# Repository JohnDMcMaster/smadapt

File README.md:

# smadapt
Socket module adapters

Released under CERN-OHL-P version 2

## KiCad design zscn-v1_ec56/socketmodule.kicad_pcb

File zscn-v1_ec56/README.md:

Allows using EC56 adapters in zscn hardware

Background:
-EC56: flash socket module ecosystem (https://www.embeddedcomputers.net/products/ParallelAdapters/)
-zscn: proprietary chip tester w/ SDIP64 socket

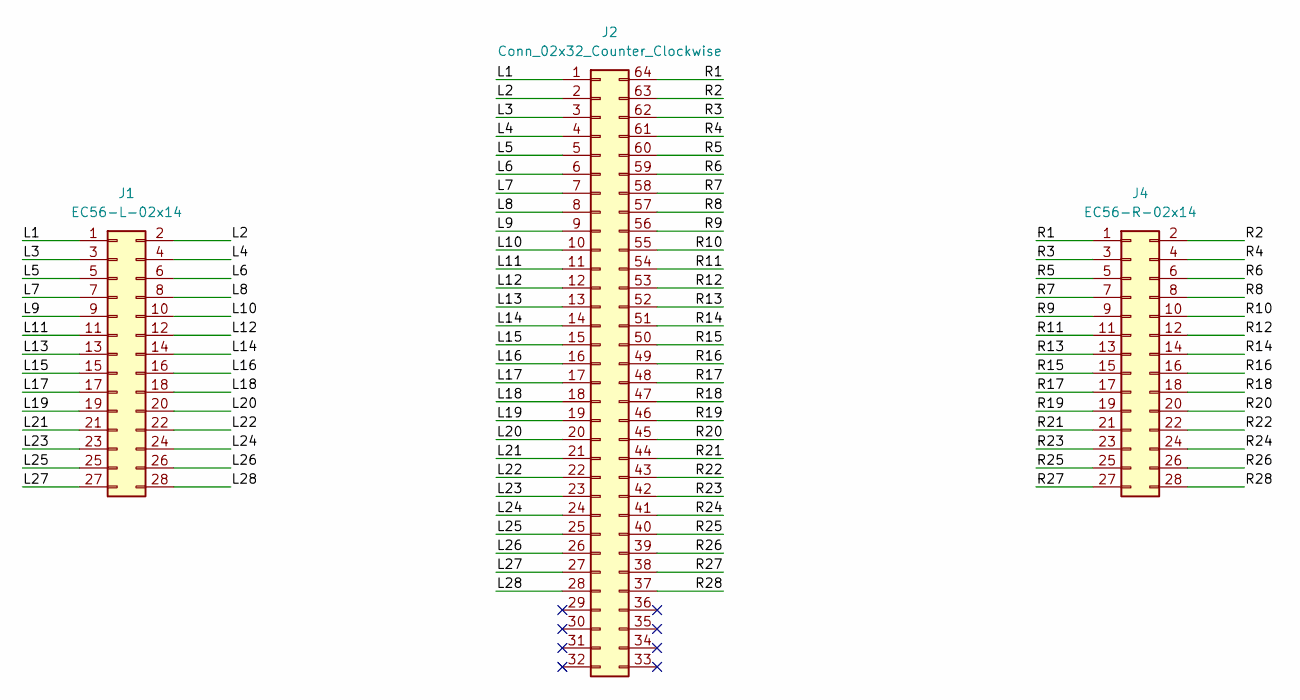
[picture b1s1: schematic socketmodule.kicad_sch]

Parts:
J1: EC56-L-02x14; PinHeader_2x14_P2.00mm_Vertical
J2: Conn_02x32_Counter_Clockwise; DIP-64_750_ELL
J4: EC56-R-02x14; PinHeader_2x14_P2.00mm_Vertical

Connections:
/L1: J1.1, J2.1
/L2: J1.2, J2.2
/L3: J1.3, J2.3
/L4: J1.4, J2.4
/L5: J1.5, J2.5
/L6: J1.6, J2.6
/L7: J1.7, J2.7
/L8: J1.8, J2.8
/L9: J1.9, J2.9
/L10: J1.10, J2.10
/L11: J1.11, J2.11
/L12: J1.12, J2.12
/L13: J1.13, J2.13
/L14: J1.14, J2.14
/L15: J1.15, J2.15
/L16: J1.16, J2.16
/L17: J1.17, J2.17
/L18: J1.18, J2.18
/L19: J1.19, J2.19
/L20: J1.20, J2.20
/L21: J1.21, J2.21
/L22: J1.22, J2.22
/L23: J1.23, J2.23
/L24: J1.24, J2.24
/L25: J1.25, J2.25
/L26: J1.26, J2.26
/L27: J1.27, J2.27
/L28: J1.28, J2.28
/R1: J2.64, J4.1
/R2: J2.63, J4.2
/R3: J2.62, J4.3
/R4: J2.61, J4.4
/R5: J2.60, J4.5
/R6: J2.59, J4.6
/R7: J2.58, J4.7
/R8: J2.57, J4.8
/R9: J2.56, J4.9
/R10: J2.55, J4.10
/R11: J2.54, J4.11
/R12: J2.53, J4.12
/R13: J2.52, J4.13
/R14: J2.51, J4.14
/R15: J2.50, J4.15
/R16: J2.49, J4.16
/R17: J2.48, J4.17
/R18: J2.47, J4.18
/R19: J2.46, J4.19
/R20: J2.45, J4.20
/R21: J2.44, J4.21
/R22: J2.43, J4.22
/R23: J2.42, J4.23
/R24: J2.41, J4.24
/R25: J2.40, J4.25
/R26: J2.39, J4.26
/R27: J2.38, J4.27
/R28: J2.37, J4.28

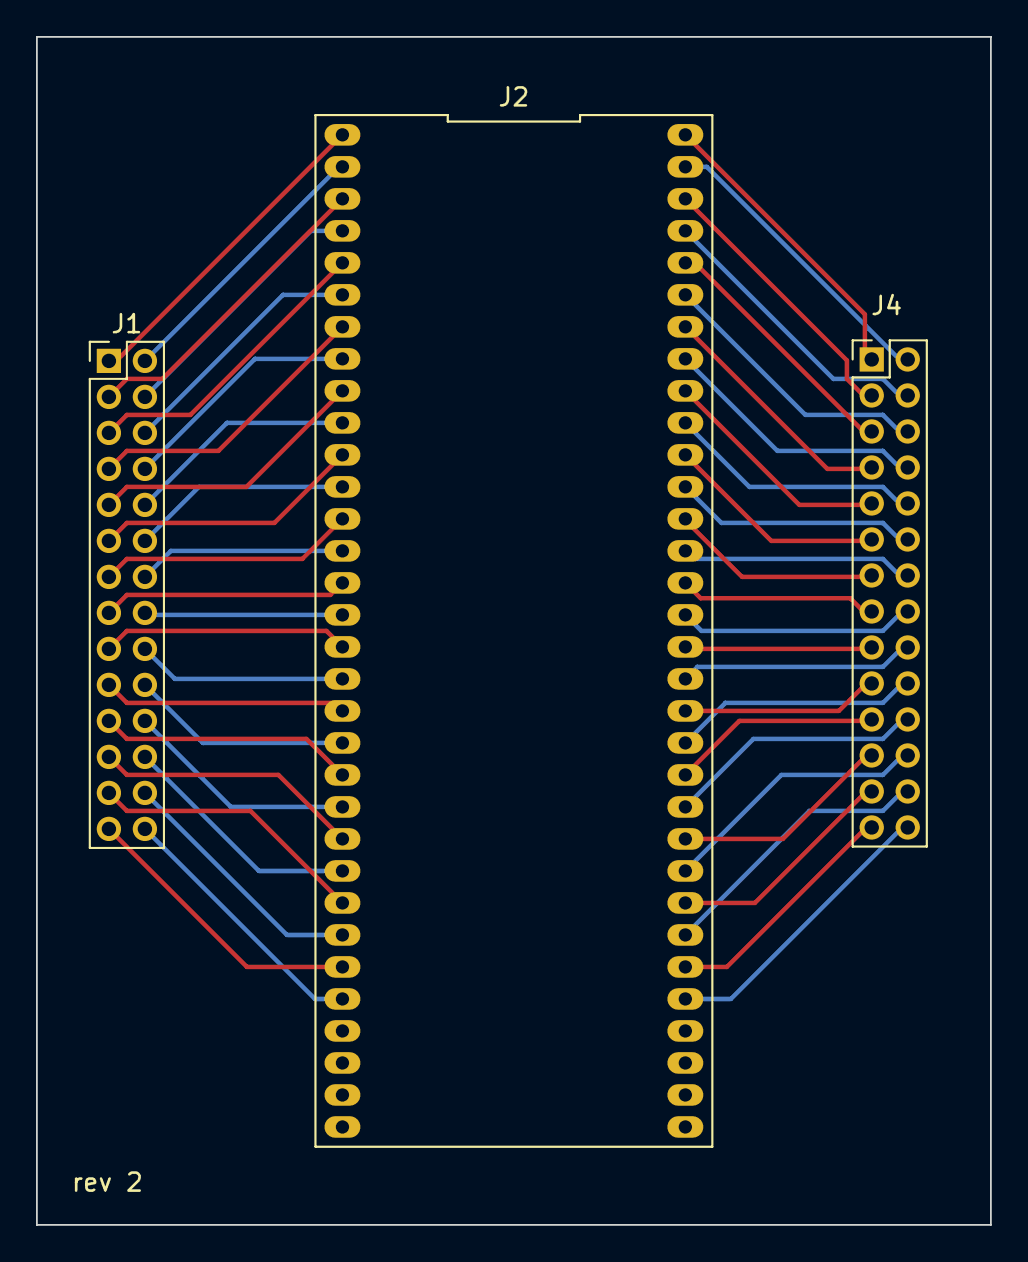
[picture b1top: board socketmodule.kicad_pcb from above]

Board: 2 copper layers, 53.0 x 66.0 mm, 3 parts (0 on the bottom side), 56 nets.

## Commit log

2022-01-19 zscn-v1_ec56 placeholder
2022-02-03 make circuit board for sdip64 to ec56
2022-03-31 fixed spacing issues rev 2
